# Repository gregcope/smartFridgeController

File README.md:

# A smart Fridge Controller

For use on a boat or other place of limited batter power to better control the Fridge.  Use Latent heat (or cool) to limit power use when on batteries by loweringh the fridge temp when there is a surplas (ie charging/motoring), and when there is less power, let the fridge temp rise a little. 

For example when Battery (VCC) volts are around 13V, which implies charging, have a target fridge temp of 2C. ie Run the compressor by making a connection. When Battery volts are less than 13V (ie not charging) aim for the fridge temp to be 6C.

# How it works

* There is a temp sensor to be placed in the fridge/coolbox to sense the fridge temp
* There is piggy back connectoin on the main battery connections to the fridge to run the device and allow it to sense Battery volts
* There is a connetion to the thermostat pins, that allows it to override the normal thermostat
* If it fails the normal thermostat works as is
* The normal theromostat should be set to the "economy" temp setting
* LEDs show the mode its in (Boost or economy, or error)

# Eagle Files

0. Uses Sparkfun DRC file
1. ERC and DRC check clean!
2. Bottom and Top Copper Pour

## Design
 
0. Uses a [Moteino](https://lowpowerlab.com/guide/moteino/)
1. The JST is to connect the VCC (Ie battery power) and Thermostat connection
2. Their is a 1.8M/3.3M VCC voltage divider to monitor the LIPO, with a 0.1uF capacitor - see [Jeelabs post here](https://jeelabs.org/2013/05/16/measuring-the-battery-without-draining-it/)
3. A 27M/3.3M voltage divider to measure 30+VCC on an ADC pin
4. Two (One for the fridge the other for ambient temp)[DS18B20 Waterproof Digital Probe Temperature Sensor with Silicone Cable (higher temp) Thermometer](https://www.ebay.co.uk/sch/i.html?_from=R40&_trksid=p2380057.m570.l1313.TR0.TRC0.H0.Xvermont+l+tent.TRS0&_nkw=DS18B20+Waterproof+Digital+Probe+Temperature+Sensor+Silicone+Cable+Thermometer&_sacat=0)
5. An efficient 7-36V to 3.3V regulator : [Murata OKI-78SR-5/1.5-W36-C](https://power.murata.com/data/power/oki-78sr.pdf)
6. [RGB LED](https://www.proto-pic.co.uk/content/datasheets/5mm_RGB_led_common_anodeDatasheet.pdf)
6. Three Status LEDS; Normal modes - Boost (blue), Economy (green) and error (red)
7. Six pin header for the two DS18 temp sensors to be connected too
8. [IXYS CPC 1706](http://www.ixysic.com/home/pdfs.nsf/www/CPC1706.pdf/$file/CPC1706.pdf) Power relay to control the compressor (ie make the connection as the thermostat does)

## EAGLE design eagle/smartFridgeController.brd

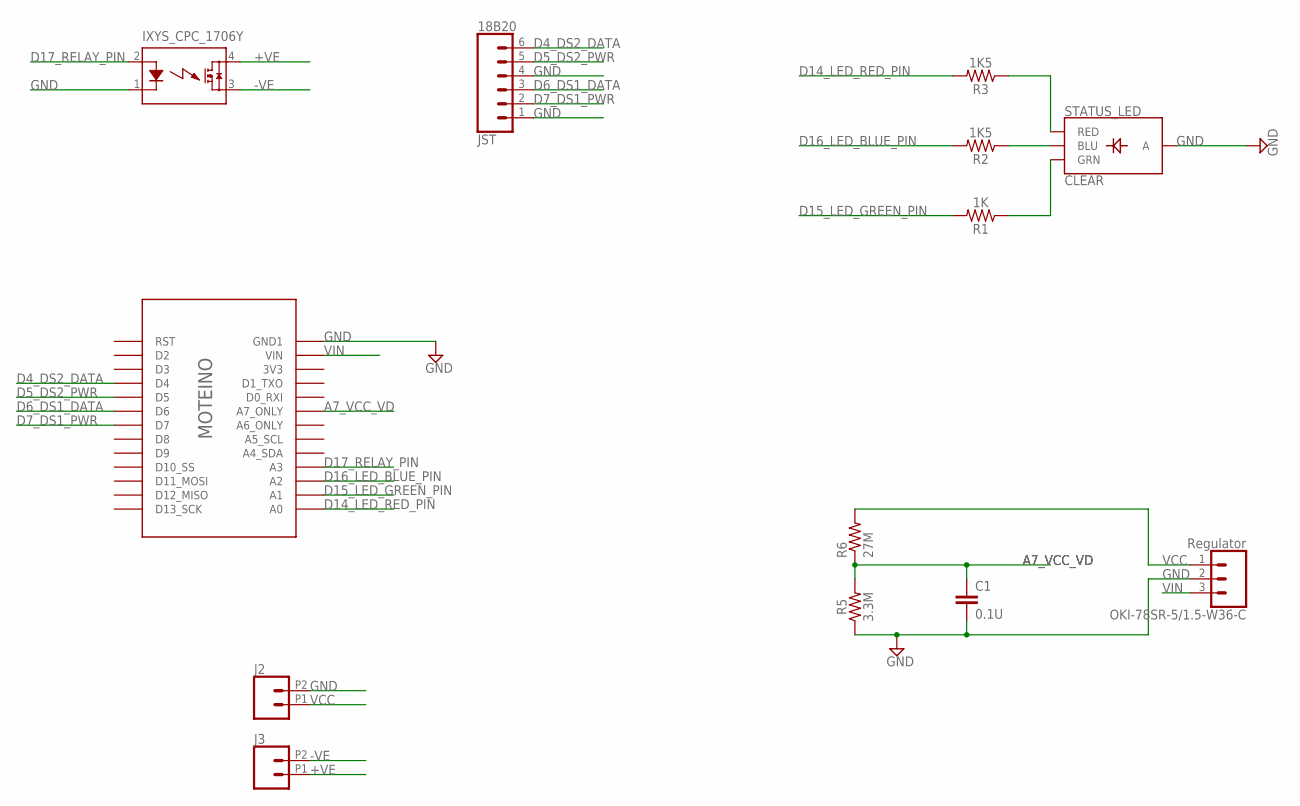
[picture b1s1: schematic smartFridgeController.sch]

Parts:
18B20: JST; 1X06
C1: 0.1U; CAP-PTH-SMALL-KIT
IXYS_CPC_1706Y: AQZ102D; AQZ-SIL04
J2, J3: CONN_022.54MM_SCREWTERM; 1X02_2.54_SCREWTERM
OKI-78SR-5/1.5-W36-C: Regulator; 1X03
R1: 1K; AXIAL-0.3
R2, R3: 1K5; AXIAL-0.3
R5: 3.3M; AXIAL-0.3
R6: 27M; 0309/12
STATUS_LED: CLEAR; LED-RGB-THRU
U$2: MOTEINO_SIMPLE

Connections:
+VE: IXYS_CPC_1706Y.4 (DS1), J3.P1 (1)
-VE: IXYS_CPC_1706Y.3 (DS2), J3.P2 (2)
A7_VCC_VD: C1.1, R5.P$2 (2), R6.1, U$2.A7_ONLY
D4_DS2_DATA: 18B20.6, U$2.D4
D5_DS2_PWR: 18B20.5, U$2.D5
D6_DS1_DATA: 18B20.3, U$2.D6
D7_DS1_PWR: 18B20.2, U$2.D7
D14_LED_RED_PIN: R3.P$2 (2), U$2.A0
D15_LED_GREEN_PIN: R1.P$2 (2), U$2.A1
D16_LED_BLUE_PIN: R2.P$2 (2), U$2.A2
D17_RELAY_PIN: IXYS_CPC_1706Y.2 (A), U$2.A3
GND: 18B20.1, 18B20.4, C1.2, IXYS_CPC_1706Y.1 (K), J2.P2 (2), OKI-78SR-5/1.5-W36-C.2, R5.P$1 (1), STATUS_LED.2 (A), U$2.GND1
unnamed: R3.P$1 (1), STATUS_LED.1 (RED)
unnamed: R2.P$1 (1), STATUS_LED.4 (BLU)
unnamed: R1.P$1 (1), STATUS_LED.3 (GRN)
VCC: J2.P1 (1), OKI-78SR-5/1.5-W36-C.1, R6.2
VIN: OKI-78SR-5/1.5-W36-C.3, U$2.VIN

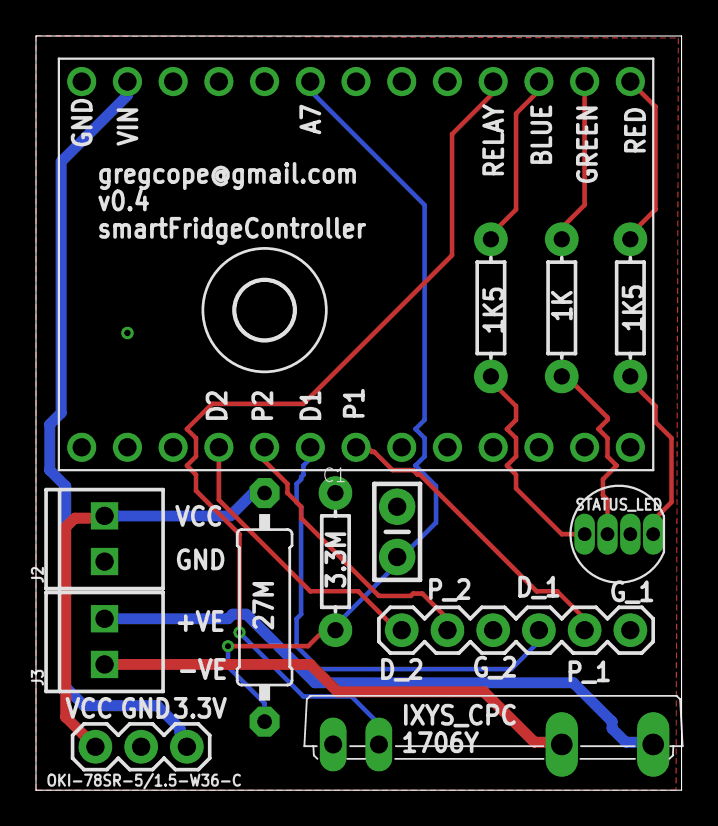
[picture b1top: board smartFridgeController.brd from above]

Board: 2 copper layers, 35.9 x 41.9 mm, 14 parts (0 on the bottom side), 17 nets.

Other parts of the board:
U$3: 3,2

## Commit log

2018-05-22 initial commit III
2018-05-22 eagle update
2018-05-22 might work
2018-05-26 Added DS header
2018-06-01 Board layed out
2018-06-02 extended board
2018-06-02 silk updates
2018-06-02 silk updates 2
2018-06-02 silk updates 3
2018-06-02 silk updates 4
2018-06-03 added 3 LEDs
2018-06-03 silkscreen updates
2018-06-03 Doco update
2018-06-03 Doco update II
2018-06-03 Doco update III
2018-06-03 Swapped IXYS pins
2018-06-04 typo
2018-06-23 Correct SIP package, large footprint
2018-06-23 Added gititgnore
2018-06-23 update layout and relay part
2018-06-25 added RGB LED
2018-06-27 simpler route, gnd pour
2018-07-03 New layout, 0.3
2018-07-07 sync
2018-07-22 Silkscreen improvemens
2018-07-22 gnd, vcc switch, labled switch on oki-78
2018-07-22 silkscreen fixes, routing 0.3
2018-07-29 Moved to screwterminal(s)

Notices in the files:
parts and their libraries:
SparkFun-Capacitors: Licensing: Creative Commons ShareAlike 4.0 International - https://creativecommons.org/licenses/by-sa/4.0
